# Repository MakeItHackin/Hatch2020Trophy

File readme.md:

Thanks for visiting this page to learn more about your HATCH trophy!  

View my YouTube video for a quick overview and demo:  
https://www.youtube.com/watch?v=jdO1fBBoojo

The trophy uses open source code and hardware, so please hack it to make it do what you want.  It comes loaded with some demo code to test each of the components.  

There will be updates to this page in the coming weeks, but if you have any questions or comments, please initiate a "Issue" on github, and I will answer as soon as I can.  

With the demo code loaded, the trophy will boot to the 'award' screen.  
Press buttons 'A' or 'B' to scroll through the menu.  
'A' and 'B' buttons serve as scrolling features through the submenus as well.  
The 'C' button is used as a 'select' button  
The 'D' button is used as a 'select' button during the 'Set Clock' Function  

When you go into the 'Demo Mode' Function, the program will loop forever.  To exit the loop, just press the reset button.  
  
The following functions are loaded with the demo software:  
View Clock (see the date/time/temperature from the DS3231 Real Time Clock module)  
Set Clock (change the clock's time)  
View Temp (see the temperature from the DS3231 Real Time Clock Module)  
Lite Sense (view the analog signal from the light sensor.  Minimum is 0 / dark and Maximum is 1023 / very very bright)  
Neopixels (cycles through a red/green/blue 'color wipe' animation)  
Buzzer (plays the Super Mario theme song)  
LEDs (cycles through LEDs on the DNA strand)  
Battery (view battery voltage)  
Demo Mode (scrolls through all features, sensors, and animations)  
  
The trophies feature the following major components:  
Arduino Nano (clone) microcontroller  
DS3231 Real Time Clock (with temperature Sensor)  
18650 Battery, along with charging circuit and DC-DC boost coverter to power the Arduino  
128x32 Pixel OLED display  
Piezo Buzzer  
Light Sensor  
Neopixel (WS2812v3) RGB LEDs  
Surface mount LEDs  
SAO v1.69 Connector

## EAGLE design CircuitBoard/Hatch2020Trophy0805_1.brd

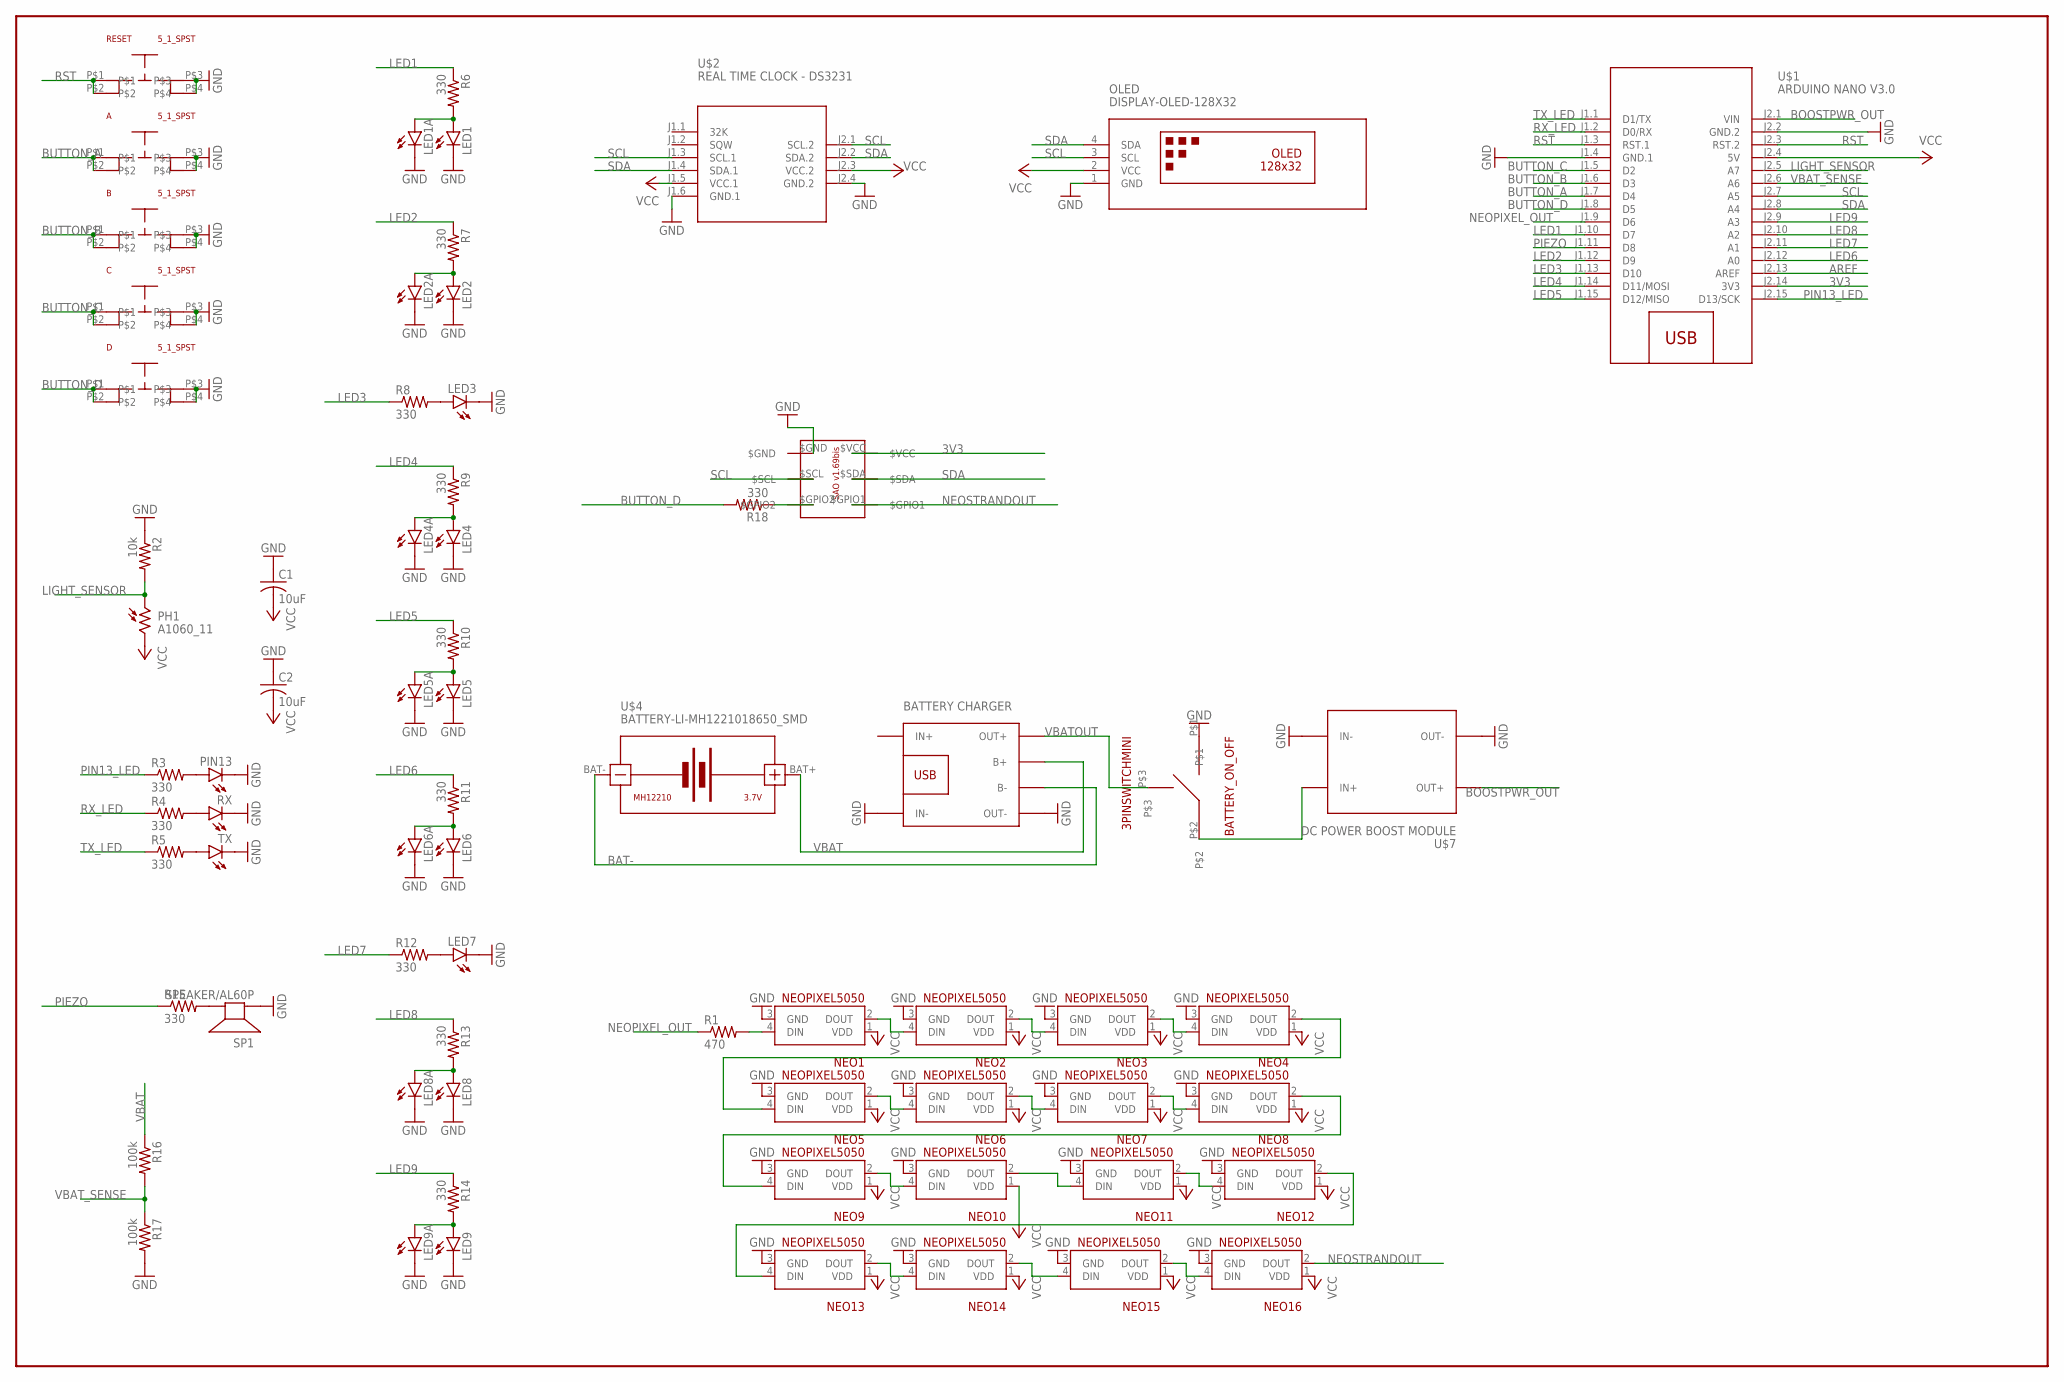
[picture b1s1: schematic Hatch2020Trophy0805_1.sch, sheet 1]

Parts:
A: 5_1_SPST
B: 5_1_SPST
BATTERY_ON_OFF: 3PINSWITCHMINI; 3PINMINI
C: 5_1_SPST
C1, C2: 10uF; C0805
D: 5_1_SPST
LED1, LED1A, LED2, LED2A, LED3, LED4, LED4A, LED5, LED5A, LED6, LED6A, LED7, LED8, LED8A, LED9, LED9A: LEDSML0805; SML0805
NEO1, NEO2, NEO3, NEO4, NEO5, NEO6, NEO7, NEO8, NEO9, NEO10, NEO11, NEO12, NEO13, NEO14, NEO15, NEO16: NEOPIXEL5050
OLED: DISPLAY-OLED-128X32
PH1: A1060_11; T0-46-A10XX
PIN13: LEDSML0805; SML0805
R1: 470; R0805
R2: 10k; R0805
R3, R4, R5, R6, R7, R8, R9, R10, R11, R12, R13, R14, R15: 330; R0805
R16, R17: 100k; R0805
R18: 330; R1206
RESET: 5_1_SPST
RX: LEDSML0805; SML0805
SP1: SPEAKER/AL60P; AL60P
TX: LEDSML0805; SML0805
U$1: ARDUINO NANO V3.0; ARDUINO-NANO-3.0
U$2: REAL TIME CLOCK - DS3231; RTC-DS3231-AT24C32
U$3: SAO-1.69; 2X3-SHROUDED-FEMALE
U$4: BATTERY-LI-MH1221018650_SMD; BATTERY_18650_SMD
U$6: BATTERY CHARGER; BAT_CHARGE_LOW_FP
U$7: DC POWER BOOST MODULE; DC-DC-STEP-UP-LOW_FP

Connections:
3V3: U$1.J2.14 (3V3), U$3.$VCC
AREF: U$1.J2.13 (AREF)
BAT-: U$4.BAT-, U$6.B-
BOOSTPWR_OUT: U$1.J2.1 (VIN), U$7.OUT+
BUTTON_A: A.P$1, A.P$2, U$1.J1.7 (D4)
BUTTON_B: B.P$1, B.P$2, U$1.J1.6 (D3)
BUTTON_C: C.P$1, C.P$2, U$1.J1.5 (D2)
BUTTON_D: D.P$1, D.P$2, R18.2, U$1.J1.8 (D5)
GND: A.P$3, A.P$4, B.P$3, B.P$4, BATTERY_ON_OFF.P$1, C.P$3, C.P$4, C1.1, C2.1, D.P$3, D.P$4, LED1.C, LED1A.C, LED2.C, LED2A.C, LED3.C, LED4.C, LED4A.C, LED5.C, LED5A.C, LED6.C, LED6A.C, LED7.C, LED8.C, LED8A.C, LED9.C, LED9A.C, NEO1.3 (GND), NEO2.3 (GND), NEO3.3 (GND), NEO4.3 (GND), NEO5.3 (GND), NEO6.3 (GND), NEO7.3 (GND), NEO8.3 (GND), NEO9.3 (GND), NEO10.3 (GND), NEO11.3 (GND), NEO12.3 (GND), NEO13.3 (GND), NEO14.3 (GND), NEO15.3 (GND), NEO16.3 (GND), OLED.1 (GND), PIN13.C, R2.1, R17.2, RESET.P$3, RESET.P$4, RX.C, SP1.1 (+), TX.C, U$1.J1.4 (GND.1), U$1.J2.2 (GND.2), U$2.J1.6 (GND.1), U$2.J2.4 (GND.2), U$3.$GND, U$6.IN-, U$6.OUT-, U$7.IN-, U$7.OUT-
LED1: R6.1, U$1.J1.10 (D7)
LED1W: LED1.A, LED1A.A, R6.2
LED2: R7.1, U$1.J1.12 (D9)
LED2W: LED2.A, LED2A.A, R7.2
LED3: R8.1, U$1.J1.13 (D10)
LED3W: LED3.A, R8.2
LED4: R9.1, U$1.J1.14 (D11/MOSI)
LED4W: LED4.A, LED4A.A, R9.2
LED5: R10.1, U$1.J1.15 (D12/MISO)
LED5W: LED5.A, LED5A.A, R10.2
LED6: R11.1, U$1.J2.12 (A0)
LED6W: LED6.A, LED6A.A, R11.2
LED7: R12.1, U$1.J2.11 (A1)
LED7W: LED7.A, R12.2
LED8: R13.1, U$1.J2.10 (A2)
LED8W: LED8.A, LED8A.A, R13.2
LED9: R14.1, U$1.J2.9 (A3)
LED9W: LED9.A, LED9A.A, R14.2
LIGHT_SENSOR: PH1.1, R2.2, U$1.J2.5 (A7)
unnamed: NEO13.2 (DOUT), NEO14.4 (DIN)
unnamed: NEO11.2 (DOUT), NEO12.4 (DIN)
unnamed: NEO12.2 (DOUT), NEO13.4 (DIN)
unnamed: NEO14.2 (DOUT), NEO15.4 (DIN)
unnamed: NEO15.2 (DOUT), NEO16.4 (DIN)
unnamed: R15.2, SP1.2 (-)
unnamed: R18.1, U$3.$GPIO2
unnamed: NEO4.2 (DOUT), NEO5.4 (DIN)
unnamed: NEO1.4 (DIN), R1.2
unnamed: NEO8.2 (DOUT), NEO9.4 (DIN)
unnamed: PIN13.A, R3.2
unnamed: R4.2, RX.A
unnamed: R5.2, TX.A
unnamed: NEO1.2 (DOUT), NEO2.4 (DIN)
unnamed: NEO2.2 (DOUT), NEO3.4 (DIN)
unnamed: NEO3.2 (DOUT), NEO4.4 (DIN)
unnamed: NEO5.2 (DOUT), NEO6.4 (DIN)
unnamed: NEO6.2 (DOUT), NEO7.4 (DIN)
unnamed: NEO7.2 (DOUT), NEO8.4 (DIN)
unnamed: NEO9.2 (DOUT), NEO10.4 (DIN)
unnamed: NEO10.2 (DOUT), NEO11.4 (DIN)
NEOPIXEL_OUT: R1.1, U$1.J1.9 (D6)
NEOSTRANDOUT: NEO16.2 (DOUT), U$3.$GPIO1
PIEZO: R15.1, U$1.J1.11 (D8)
PIN13_LED: R3.1, U$1.J2.15 (D13/SCK)
RST: RESET.P$1, RESET.P$2, U$1.J1.3 (RST.1), U$1.J2.3 (RST.2)
RX_LED: R4.1, U$1.J1.2 (D0/RX)
SCL: OLED.3 (SCL), U$1.J2.7 (A5), U$2.J1.3 (SCL.1), U$2.J2.1 (SCL.2), U$3.$SCL
SDA: OLED.4 (SDA), U$1.J2.8 (A4), U$2.J1.4 (SDA.1), U$2.J2.2 (SDA.2), U$3.$SDA
TX_LED: R5.1, U$1.J1.1 (D1/TX)
VBAT: R16.1, U$4.BAT+, U$6.B+
VBATOUT: BATTERY_ON_OFF.P$3, U$6.OUT+
VBAT_SENSE: R16.2, R17.1, U$1.J2.6 (A6)
VBOOST_IN: BATTERY_ON_OFF.P$2, U$7.IN+
VCC: C1.2, C2.2, NEO1.1 (VDD), NEO2.1 (VDD), NEO3.1 (VDD), NEO4.1 (VDD), NEO5.1 (VDD), NEO6.1 (VDD), NEO7.1 (VDD), NEO8.1 (VDD), NEO9.1 (VDD), NEO10.1 (VDD), NEO11.1 (VDD), NEO12.1 (VDD), NEO13.1 (VDD), NEO14.1 (VDD), NEO15.1 (VDD), NEO16.1 (VDD), OLED.2 (VCC), PH1.2, U$1.J2.4 (5V), U$2.J1.5 (VCC.1), U$2.J2.3 (VCC.2)

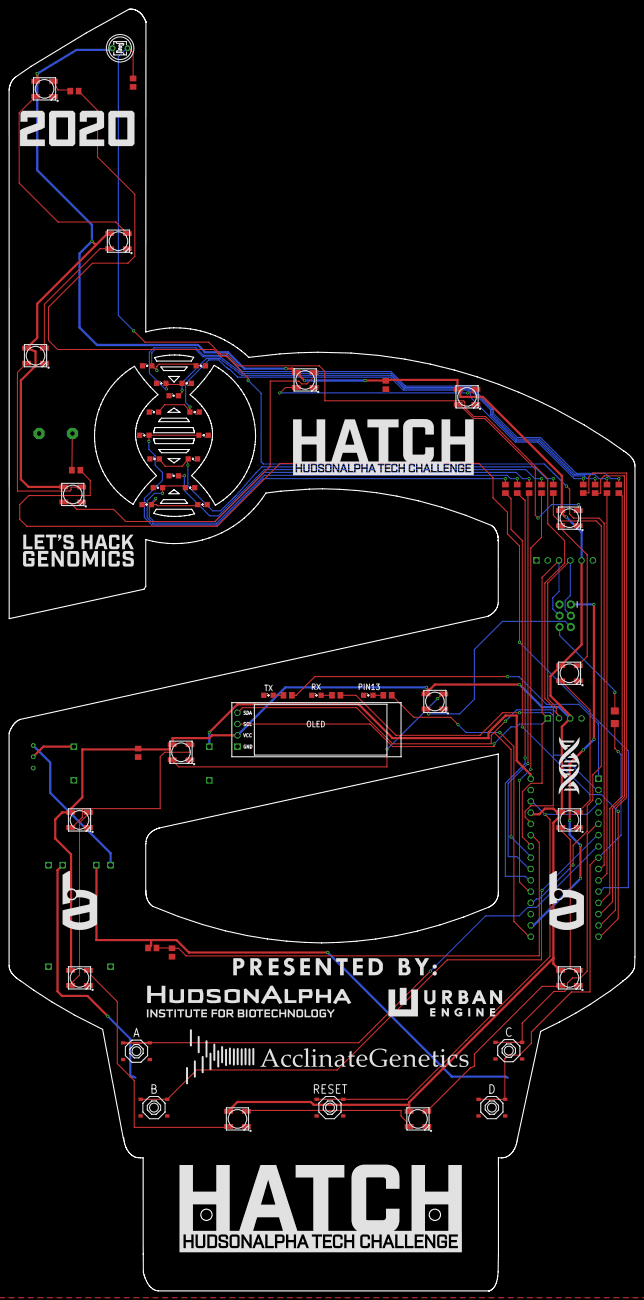
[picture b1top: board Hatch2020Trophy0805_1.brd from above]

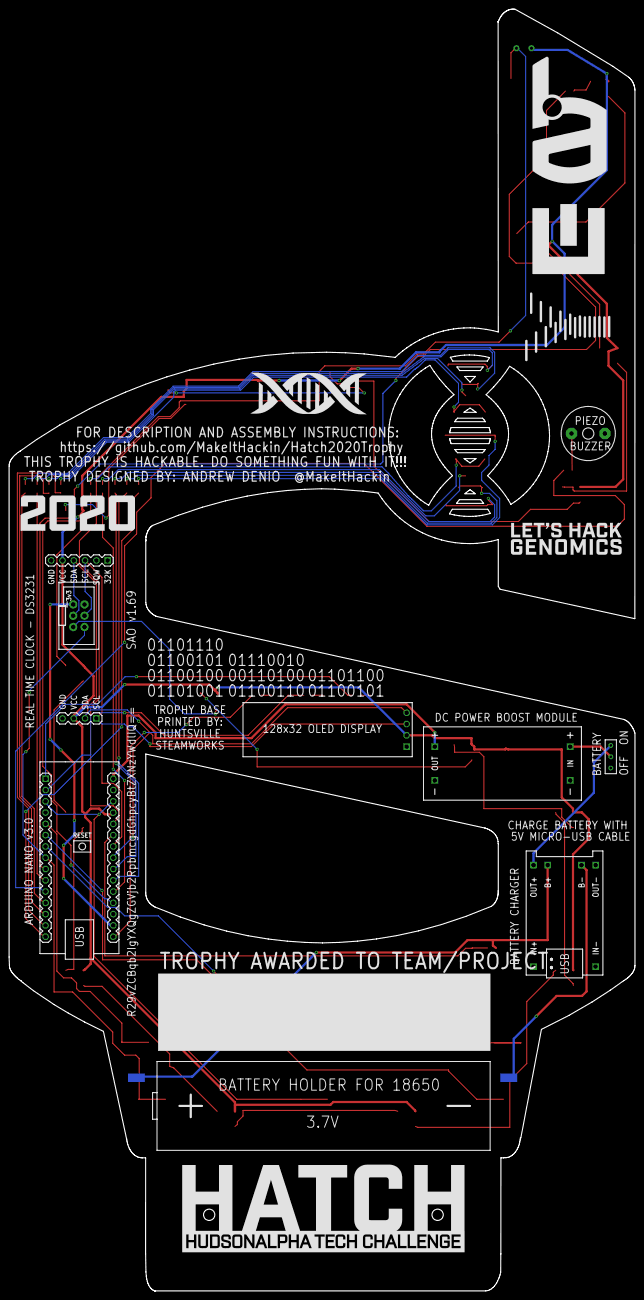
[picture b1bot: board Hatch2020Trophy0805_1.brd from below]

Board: 2 copper layers, 140.9 x 288.6 mm, 70 parts (7 on the bottom side), 62 nets.

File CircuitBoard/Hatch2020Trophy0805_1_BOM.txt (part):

Partlist exported from C:/Users/Andrew/Documents/EAGLE/projects/HATCH 2020 Trophy/Hatch2020Trophy0805_1.sch at 2/18/2020 12:30 PM

Part           Value                       Device                        Package              Description                                                                                                       POPULARITY SPICEPREFIX
A              5_1_SPST                    5_1_SPST                      5_1_SPST                                                                                                                                                     
B              5_1_SPST                    5_1_SPST                      5_1_SPST                                                                                                                                                     
BATTERY_ON_OFF 3PINSWITCHMINI              3PINSWITCHMINI                3PINMINI                                                                                                                                                     
C              5_1_SPST                    5_1_SPST                      5_1_SPST                                                                                                                                                     
C1             10uF                        C-USC0805                     C0805                CAPACITOR, American symbol                                                                                        63         C          
C2             10uF                        C-USC0805                     C0805                CAPACITOR, American symbol                                                                                        63         C          
D              5_1_SPST                    5_1_SPST                      5_1_SPST                                                                                                                                                     
LED1                                       LEDSML0805                    SML0805              LED                                                                                                               17                    
LED1A                                      LEDSML0805                    SML0805              LED                                                                                                               17                    
LED2                                       LEDSML0805                    SML0805              LED                                                                                                               17                    
LED2A                                      LEDSML0805                    SML0805              LED                                                                                                               17                    
LED3                                       LEDSML0805                    SML0805              LED                                                                                                               17                    
LED4                                       LEDSML0805                    SML0805              LED                                                                                                               17                    
LED4A                                      LEDSML0805                    SML0805              LED                                                                                                               17                    
LED5                                       LEDSML0805                    SML0805              LED                                                                                                               17                    
LED5A                                      LEDSML0805                    SML0805              LED                                                                                                               17                    
LED6                                       LEDSML0805                    SML0805              LED                                                                                                               17                    
LED6A                                      LEDSML0805                    SML0805              LED                                                                                                               17                    
LED7                                       LEDSML0805                    SML0805              LED                                                                                                               17                    
LED8                                       LEDSML0805                    SML0805              LED                                                                                                               17                    
LED8A                                      LEDSML0805                    SML0805              LED                                                                                                               17                    
LED9                                       LEDSML0805                    SML0805              LED                                                                                                               17                    
LED9A                                      LEDSML0805                    SML0805              LED                                                                                                               17                    
NEO1           NEOPIXEL5050                NEOPIXEL5050                  NEOPIXEL5050                                                                                                                                                 
NEO2           NEOPIXEL5050                NEOPIXEL5050                  NEOPIXEL5050                                                                                                                                                 
NEO3           NEOPIXEL5050                NEOPIXEL5050                  NEOPIXEL5050                                                                                                                                                 
NEO4           NEOPIXEL5050                NEOPIXEL5050                  NEOPIXEL5050                                                                                                                                                 
NEO5           NEOPIXEL5050                NEOPIXEL5050                  NEOPIXEL5050                                                                                                                                                 
NEO6           NEOPIXEL5050                NEOPIXEL5050                  NEOPIXEL5050                                                                                                                                                 
NEO7           NEOPIXEL5050                NEOPIXEL5050                  NEOPIXEL5050                                                                                                                                                 
NEO8           NEOPIXEL5050                NEOPIXEL5050                  NEOPIXEL5050                                                                                                                                                 
NEO9           NEOPIXEL5050                NEOPIXEL5050                  NEOPIXEL5050                                                                                                                                                 
NEO10          NEOPIXEL5050                NEOPIXEL5050                  NEOPIXEL5050                                                                                                                                                 
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
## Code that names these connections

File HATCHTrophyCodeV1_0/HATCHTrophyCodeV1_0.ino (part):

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// on a live circuit...if you must, connect GND first.

// Assign Input Pins (Buttons and Light sensor)
#define BUTTON_A_PIN 4
#define BUTTON_B_PIN 3
#define BUTTON_C_PIN 2
#define BUTTON_D_PIN 5
#define BATTERY_VOLTAGE_PIN A6
#define LIGHT_SENSOR_PIN A7
#define BUZZER_PIN 8

// LED Pin Assignments
int RX_LED_PIN = 0;
int TX_LED_PIN = 1;
int OnBoardLED_PIN = 13;
int LED_1_PIN = 7;
int LED_2_PIN = 9;
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int LED_8_PIN = A2;
int LED_9_PIN = A3;

int NewLEDArray[] = {LED_1_PIN, LED_2_PIN, LED_3_PIN, LED_4_PIN, LED_5_PIN, LED_6_PIN, LED_7_PIN, LED_8_PIN, LED_9_PIN, OnBoardLED_PIN, RX_LED_PIN, TX_LED_PIN};
const int NewLEDArrayLength = sizeof(NewLEDArray) / sizeof(NewLEDArray[0]);

// New and Old state variables used for Buttons
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  colorWipe(strip.Color(0, 0, 0), 0); // Turn Off
  
  //Setup input pins
  pinMode(BUTTON_A_PIN, INPUT_PULLUP);
  pinMode(BUTTON_B_PIN, INPUT_PULLUP);
  pinMode(BUTTON_C_PIN, INPUT_PULLUP);
  pinMode(BUTTON_D_PIN, INPUT_PULLUP);
  pinMode(BATTERY_VOLTAGE_PIN, INPUT);
  pinMode(LIGHT_SENSOR_PIN, INPUT);

  //Setup output pins
  pinMode(BUZZER_PIN,OUTPUT);
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void CheckbuttonA(){

    // Get current button state.
  buttonANewState = digitalRead(BUTTON_A_PIN);

  // Check if state changed from high to low (button press).
  if (buttonANewState == LOW && buttonAOldState == HIGH) {
    // Short delay to debounce button.
    delay(20);
    // Check if button is still low after debounce.
    buttonANewState = digitalRead(BUTTON_A_PIN);
    if (buttonANewState == LOW) {
      // BUTTON PRESSED
     Serial.println("BUTTON A PRESSED");
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void CheckbuttonB(){

    // Get current button state.
  buttonBNewState = digitalRead(BUTTON_B_PIN);

  // Check if state changed from high to low (button press).
  if (buttonBNewState == LOW && buttonBOldState == HIGH) {
    // Short delay to debounce button.
    delay(20);
    // Check if button is still low after debounce.
    buttonBNewState = digitalRead(BUTTON_B_PIN);
    if (buttonBNewState == LOW) {
      // BUTTON PRESSED
     Serial.println("BUTTON B PRESSED");
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void CheckbuttonC(){

    // Get current button state.
  buttonCNewState = digitalRead(BUTTON_C_PIN);

  // Check if state changed from high to low (button press).
  if (buttonCNewState == LOW && buttonCOldState == HIGH) {
    // Short delay to debounce button.
    delay(20);
    // Check if button is still low after debounce.
    buttonCNewState = digitalRead(BUTTON_C_PIN);
    if (buttonCNewState == LOW) {
      // BUTTON PRESSED
     Serial.println("BUTTON C PRESSED");
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void CheckbuttonD(){

    // Get current button state.
  buttonDNewState = digitalRead(BUTTON_D_PIN);

  // Check if state changed from high to low (button press).
  if (buttonDNewState == LOW && buttonDOldState == HIGH) {
    // Short delay to debounce button.
    delay(20);
    // Check if button is still low after debounce.
    buttonDNewState = digitalRead(BUTTON_D_PIN);
    if (buttonDNewState == LOW) {
      // BUTTON PRESSED
     Serial.println("BUTTON D PRESSED");
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  display.setCursor(0,0);
  //display.setTextSize(2);
  display.print("VALUE ");
  display.print(analogRead(LIGHT_SENSOR_PIN));
  display.println(" ");
  display.setTextSize(1);
  display.println("MIN (DARK): 0   ");
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    display.println("LIGHT SENSOR VALUE");
    display.setCursor(35,10);
    display.setTextSize(3);
    display.print(analogRead(LIGHT_SENSOR_PIN));
    display.println(" ");
    display.display();
    delay(50);
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
  //delay(50);

  while (digitalRead(BUTTON_D_PIN) == HIGH) {
        if (digitalRead(BUTTON_B_PIN) == LOW) {
          ////display.setCursor(0,35);
          ////display.print("    ");
        NewHour++;
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       delay(50);
        }
      }
            if (digitalRead(BUTTON_A_PIN) == LOW) {
          ////display.setCursor(0,35);
          ////display.print("    ");
        NewHour--;
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
delay(500);

  while (digitalRead(BUTTON_D_PIN) == HIGH) {
        if (digitalRead(BUTTON_B_PIN) == LOW) {
          //display.setCursor(0,35);
          //display.print("    ");
        NewMinute++;
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       delay(50);
        }
      }
        if (digitalRead(BUTTON_A_PIN) == LOW) {
          //display.setCursor(0,35);
          //display.print("    ");
        NewMinute--;
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
delay(500);

  while (digitalRead(BUTTON_D_PIN) == HIGH) {
        if (digitalRead(BUTTON_B_PIN) == LOW) {
         //// display.setCursor(0,35);
        ////  display.print("    ");
        NewSecond++;
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       delay(50);
        }
      }
        if (digitalRead(BUTTON_A_PIN) == LOW) {
         //// display.setCursor(0,35);
        ////  display.print("    ");
        NewSecond--;
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  NewYear = 2020;
}

  while (digitalRead(BUTTON_D_PIN) == HIGH) {
        if (digitalRead(BUTTON_B_PIN) == LOW) {
          //display.setCursor(0,35);
          //display.print("    ");
        NewYear++;
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       delay(50);
        }
      }
        if (digitalRead(BUTTON_A_PIN) == LOW) {
          //display.setCursor(0,35);
          //display.print("    ");
        NewYear--;
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
delay(500);

  while (digitalRead(BUTTON_D_PIN) == HIGH) {
        if (digitalRead(BUTTON_B_PIN) == LOW) {
         // display.setCursor(0,35);
         // display.print("    ");
        NewMonth++;
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       delay(50);
        }
      }
        if (digitalRead(BUTTON_A_PIN) == LOW) {
         // display.setCursor(0,35);
         // display.print("    ");
        NewMonth--;
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
delay(500);

  while (digitalRead(BUTTON_D_PIN) == HIGH) {
        if (digitalRead(BUTTON_B_PIN) == LOW) {
          //display.setCursor(0,35);
          //display.print("    ");
        NewDate++;
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        }

      }
if (digitalRead(BUTTON_A_PIN) == LOW) {
          //display.setCursor(0,35);
          //display.print("    ");
        NewDate--;
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  }
  if (LightSensorMenuSelected == 1){
    for (int i = 0; i < 100; i++)  {
////       printLEDNumber(analogRead(LIGHT_SENSOR_PIN)); 
       delay(150);     
    }
////    quadDisplayString("----");   
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

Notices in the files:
parts and their libraries:
diy-modules: Released under the Creative Commons Attribution 4.0 International License: http://creativecommons.org/licenses/by/4.0
